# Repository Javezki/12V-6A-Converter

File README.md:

# About This Project

Hello everyone!  
This is a 12V/5V 8A adjustable buck converter I designed for a design team (96W Converter on a good day).

-1.png>)

This version of the board is untested, but the core functionality (the converting) has been tested and it works pretty well.

## JLC Note

Every component on the board has a JLC#.  
You just need to solder your own automotive blade fuse holder (3557-2) and Molex Mini Fit Jrs (1726480102)—**though these connectors and the fuse holder can technically also be assembled by JLC, just at additional expense**.  
Approximate cost is ~40 CAD for 2 boards assembled, 2 week shipping, but could vary.

## Connector Note

It's a little tricky crimping those, but you can do it with a basic JST crimper.

## Other Functionality

- Automotive blade fuse and a PFET for reverse polarity protection present  
- Gold fingers for a slot card mount  
- Core chip: SIC438BED-T1-GE3 (large package, but JLC can assemble it with no problem)

# Tested Functionality

- 12V 6A works at 300 kHz switching frequency (Vin: 13.2V) with a thermal rise of about ~25°C  
- 5V 6A works at 750 kHz switching frequency (Vin: 13.2V) with a thermal rise of about ~10°C  
- Tests conducted with an electronic load, varying the current, and measuring temperature with a thermocouple  
- For higher voltage input: use 750 kHz for the 12V rail (calculate max duty cycle using the SIC438BED-T1-GE3 datasheet)

# Untested Functionality

- Reverse polarity protection was only simulated in MultiSim—untested in hardware due to costs  
- Jumpers for swapping 12V/5V and switching frequency are untested (just resistor swapping, so risk is minimal)  
- Board theoretically runs at 8A (no OCP trip at full load, chip rated 8A), but output ripple and full thermal capability aren't fully characterized. **Use at your own risk.**

# Things To Clean Up

- All JLC component footprint references are messed up because of a switch to KiCad 9  
- 3D models for all components need to be added eventually (on the todo list)  
- Better test pad layout is coming in a future revision  
- Replace the PFET with a proper reverse polarity charge pump IC for a high-side NFET (lower Rds(on), less heat)  
- Want different connectors? Let me know, or just mod the files yourself—they're on the page!

# Schematic

# Final Remarks

- 2-layer board build *might not work*—JLC assembly doesn't support this IC on 2 layer builds (success rate ~10%)  
- 4-layer assembly has been issue-free so far  
- If you want to fund more testing, DM me on Discord @javezki

Love y'all

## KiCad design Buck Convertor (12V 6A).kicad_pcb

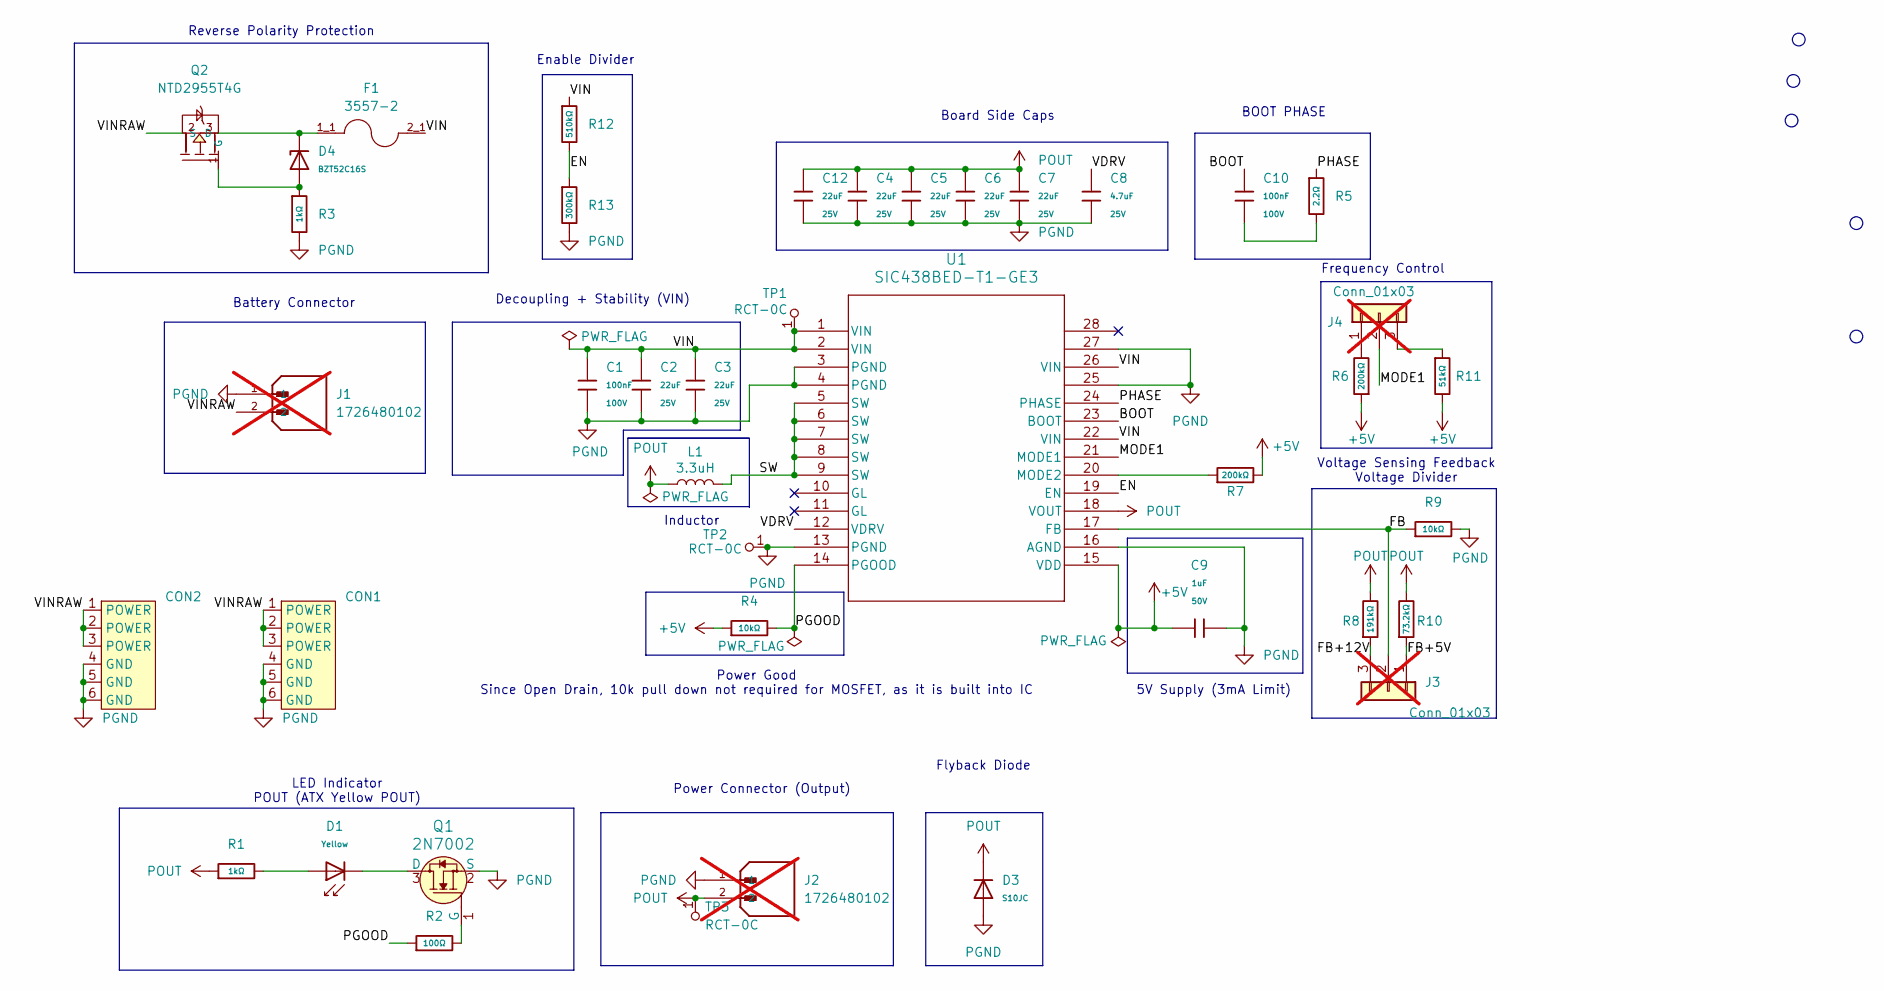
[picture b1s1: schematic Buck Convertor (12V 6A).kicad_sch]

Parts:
C1, C10: 100nF; C_0805; Voltage Rated 100V; Tolerance ±10%; Part CL21B104KCFNNNE; LCSC C28233
C2, C3, C4, C5, C6, C7, C12: 22uF; C_0805; Voltage Rated 25V; Tolerance ±20%; Part CL21A226MAQNNNE; LCSC C45783
C8: 4.7uF; C_0805; Voltage Rated 25V; Tolerance ±10%; Part CL21A475KAQNNNE; LCSC C1779
C9: 1uF; C_0805; Voltage Rated 50V; Tolerance ±10%; Part CL21B105KBFNNNE; LCSC C28323
CON1, CON2: 6 Contact Gold Finger
D1: Yellow; D_0805; Part KT-0805Y; LCSC C2296
D3: S10JC; D_SMC; Part S10JC; LCSC C18199110
D4: BZT52C16S; D_SOD-323; Zener Voltage (Range) 15.3V~17.1V; Zener Voltage (Nom) 16V; Part BZT52C16S; LCSC C19077449
F1: 3557-2; FUSE_3557-2; PARTREV D
J1, J2: 1726480102; CONN_SD-172648-0000_02_MOL; PARTREV A2; not fitted
J3, J4: Conn_01x03; PinHeader_1x03_P1.27mm_Vertical; not fitted
L1: 3.3uH; ZEMS1040; LCSC C41415637
Q1: 2N7002; SOT-23-3; MPN 2N7002; Digi-Key_PN 2N7002NCT-ND
Q2: NTD2955T4G; TO-252-2_L6.6-W6.1-P4.57-LS9.9-TL-CW; LCSC C10663
R1, R3: 1kΩ; R_0805; Overload Voltage (Max) 150V; Tolerance ±1%; Part 0805W8F1001T5E; LCSC C17513
R2: 100Ω; R_0805; Overload Voltage (Max) 150V; Tolerance ±1%; Part 0805W8F1000T5E; LCSC C17408
R4, R9: 10kΩ; R_0805; Overload Voltage (Max) 150V; Tolerance ±1%; Part 0805W8F1002T5E; LCSC C17414
R5: 2.2Ω; R_0805; Overload Voltage (Max) 150V; Tolerance ±1%; Part 0805W8F220KT5E; LCSC C17521
R6, R7: 200kΩ; R_0805; Overload Voltage (Max) 150V; Tolerance ±1%; Part 0805W8F2003T5E; LCSC C17539
R8: 191kΩ; R_0805; LCSC C17511
R10: 73.2kΩ; R_0805; LCSC C17814
R11: 51kΩ; R_0805; Overload Voltage (Max) 150V; Tolerance ±1%; Part 0805W8F5102T5E; LCSC C17737
R12: 510kΩ; R_0805; Overload Voltage (Max) 150V; Tolerance ±1%; Part 0805W8F5103T5E; LCSC C17733
R13: 300kΩ; R_0805; Overload Voltage (Max) 150V; Tolerance ±1%; Part 0805W8F3003T5E; LCSC C17616
TP1, TP2, TP3: RCT-0C; PROBE_PAD_0805; MPN RCT-0C; Digi-Key_PN A106144CT-ND
U1: SIC438BED-T1-GE3; QFN_ED-T1-GE3_VIS; LCSC C511430

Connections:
+5V: C9.1, R4.1, R6.1, R7.2, R11.2, U1.15 (VDD)
/BOOT: C10.2, U1.23 (BOOT)
/EN: R12.2, R13.1, U1.19 (EN)
/FB: J3.2, R9.1, U1.17 (FB)
/FB+5V: J3.1, R10.2
/FB+12V: J3.3, R8.2
/MODE1: J4.2, U1.21 (MODE1)
/PGOOD: R2.1, R4.2, U1.14 (PGOOD)
/PHASE: R5.1, U1.24 (PHASE)
/SW: L1.2, U1.5 (SW), U1.6 (SW), U1.7 (SW), U1.8 (SW), U1.9 (SW)
/VDRV: C8.1, U1.12 (VDRV)
/VIN: C1.1, C2.1, C3.1, F1.2_1, R12.1, TP1.1, U1.1 (VIN), U1.2 (VIN), U1.22 (VIN), U1.26 (VIN)
/VINRAW: CON1.1 (POWER), CON1.2 (POWER), CON1.3 (POWER), CON2.1 (POWER), CON2.2 (POWER), CON2.3 (POWER), J1.2, Q2.2 (D)
unnamed: C10.1, R5.2
unnamed: D1.2, R1.2
unnamed: J4.1, R6.2
unnamed: J4.3, R11.1
unnamed: D1.1, Q1.3 (D)
unnamed: Q1.1 (G), R2.2
unnamed: D4.2, Q2.1 (G), R3.1
unnamed: D4.1, F1.1_1, Q2.3 (S)
unnamed: R7.1, U1.20 (MODE2)
PGND: C1.2, C2.2, C3.2, C4.2, C5.2, C6.2, C7.2, C8.2, C9.2, C12.2, CON1.4 (GND), CON1.5 (GND), CON1.6 (GND), CON2.4 (GND), CON2.5 (GND), CON2.6 (GND), D3.2, J1.1, J2.1, Q1.2 (S), R3.2, R9.2, R13.2, TP2.1, U1.3 (PGND), U1.4 (PGND), U1.13 (PGND), U1.16 (AGND), U1.25, U1.27
POUT: C4.1, C5.1, C6.1, C7.1, C12.1, D3.1, J2.2, L1.1, R1.1, R8.1, R10.1, TP3.1, U1.18 (VOUT)

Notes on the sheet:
Battery Connector
Power Good Since Open Drain, 10k pull down not required for MOSFET, as it is built into IC
Board Side Caps
5V Supply (3mA Limit)
Inductor
Decoupling + Stability (VIN)
LED Indicator POUT (ATX Yellow POUT)
Frequency Control
Reverse Polarity Protection
Power Connector (Output)
BOOT PHASE
Voltage Sensing Feedback Voltage Divider
Flyback Diode
Enable Divider

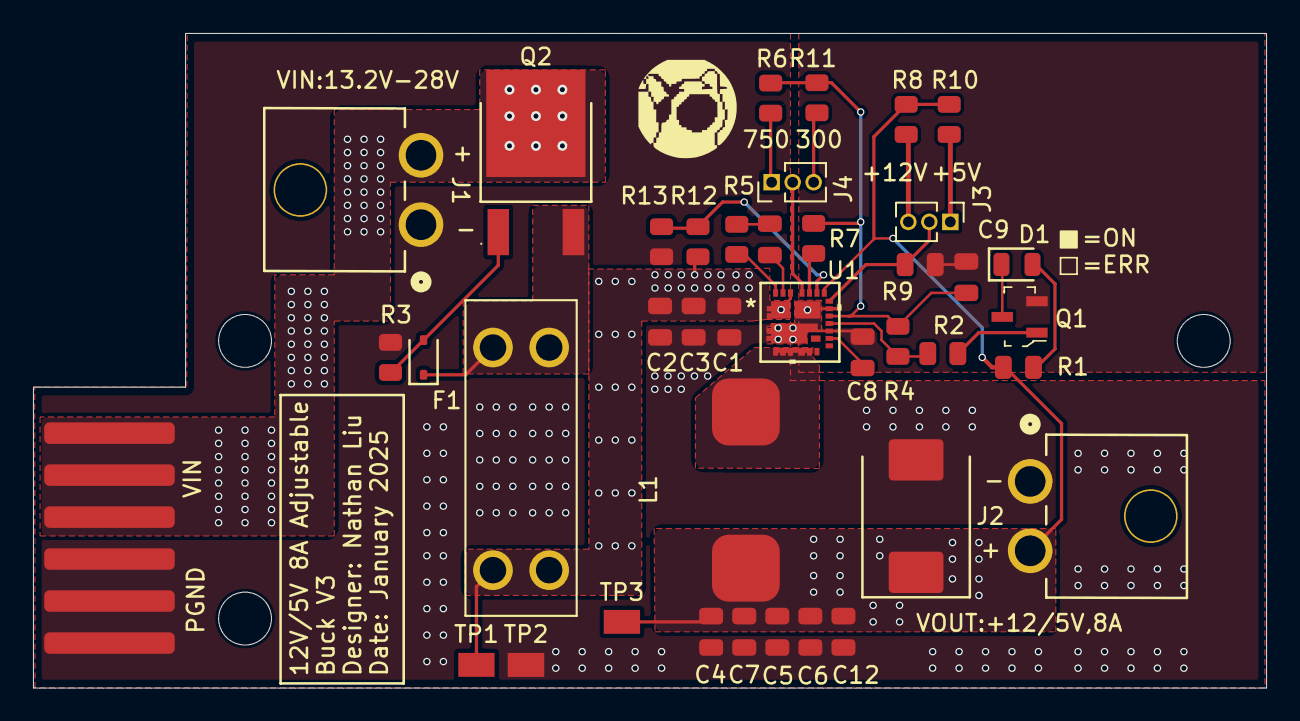
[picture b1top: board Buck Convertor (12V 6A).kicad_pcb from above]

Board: 4 copper layers, 74.6 x 39.6 mm, 41 parts (1 on the bottom side), 24 nets.

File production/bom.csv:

Designator,Footprint,Quantity,Value,LCSC Part #
"C1, C10",C_0805,2,100nF,C28233
"C12, C2, C3, C4, C5, C6, C7",C_0805,7,22uF,C45783
C8,C_0805,1,4.7uF,C1779
C9,C_0805,1,1uF,C28323
"CON1, CON2",6 Contact Gold Finger,2,~,
D1,D_0805,1,Yellow,C2296
D3,D_SMC,1,S10JC,C18199110
D4,D_SOD-323,1,BZT52C16S,C19077449
F1,FUSE_3557-2,1,3557-2,
"GND, VIN, VOUT",PROBE_PAD_0805,3,RCT-0C,RCT-0C
L1,ZEMS1040,1,3.3uH,C41415637
Q1,SOT-23-3,1,2N7002,C8545
Q2,DPAK-369C_ONS,1,NTD2955T4G,C10663
"R1, R3",R_0805,2,1kΩ,C17513
R10,R_0805,1,73.2kΩ,C17814
R11,R_0805,1,51kΩ,C17737
R12,R_0805,1,510kΩ,C17733
R13,R_0805,1,300kΩ,C17616
R2,R_0805,1,100Ω,C17408
"R4, R9",R_0805,2,10kΩ,C17414
R5,R_0805,1,2.2Ω,C17521
"R6, R7",R_0805,2,200kΩ,C17539
R8,R_0805,1,191kΩ,C17511
U1,QFN_ED-T1-GE3_VIS,1,SIC438BED-T1-GE3,C511430

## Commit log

2025-09-13 Initial Commit
    All files of 12V/5V 8A buck converter project available for JLCPCB
2025-09-13 Fixed PFET being wrong size
2025-09-13 Added 3D render and updated README
2025-09-13 Update README with JLC and connector notes
    Added notes about JLC components, connectors, and other functionalities.
2025-09-13 Revise README for improved clarity and detail
